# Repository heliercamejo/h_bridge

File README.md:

# H Bridge circuit
This circuit was following electronoobs youtube channel tutorial

[H_BRIDGE](https://electronoobs.com/eng_circuitos_tut1.php)

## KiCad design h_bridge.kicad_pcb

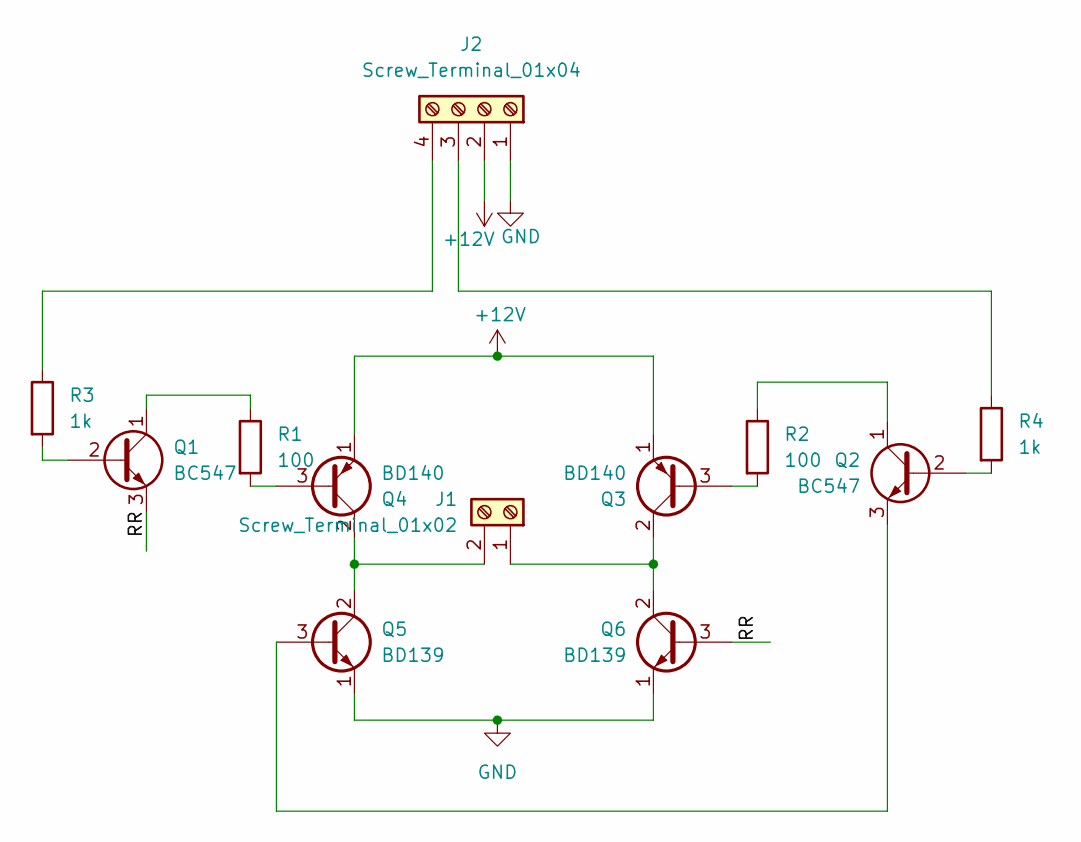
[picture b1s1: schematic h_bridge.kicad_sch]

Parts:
J1: Screw_Terminal_01x02; TerminalBlock_Phoenix_MKDS-1,5-2-5.08_1x02_P5.08mm_Horizont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
J2: Screw_Terminal_01x04; TerminalBlock_Phoenix_MKDS-1,5-4-5.08_1x04_P5.08mm_Horizont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
Q1, Q2: BC547; TO-92_Inline
Q3, Q4: BD140; TO-126-3_Vertical
Q5, Q6: BD139; TO-126-3_Vertical
R1, R2: 100; R_Axial_DIN0204_L3.6mm_D1.6mm_P7.62mm_Horizontal
R3, R4: 1k; R_Axial_DIN0204_L3.6mm_D1.6mm_P7.62mm_Horizontal

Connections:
+12V: J2.2, Q3.1 (E), Q4.1 (E)
/RR: Q1.3 (E), Q6.3 (B)
GND: J2.1, Q5.1 (E), Q6.1 (E)
unnamed: J1.1, Q3.2 (C), Q6.2 (C)
unnamed: J1.2, Q4.2 (C), Q5.2 (C)
unnamed: J2.3, R4.1
unnamed: J2.4, R3.1
unnamed: Q1.2 (B), R3.2
unnamed: Q1.1 (C), R1.1
unnamed: Q2.2 (B), R4.2
unnamed: Q2.1 (C), R2.1
unnamed: Q2.3 (E), Q5.3 (B)
unnamed: Q3.3 (B), R2.2
unnamed: Q4.3 (B), R1.2

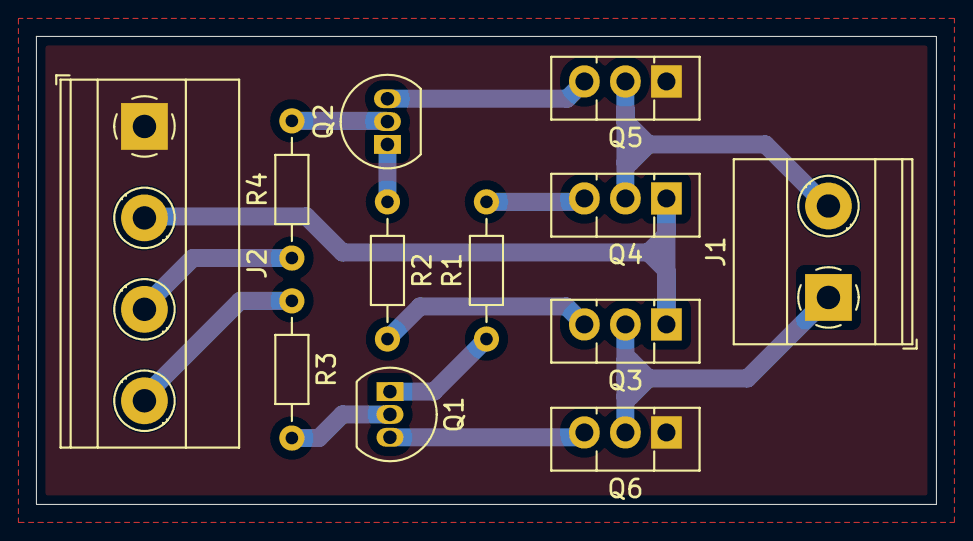
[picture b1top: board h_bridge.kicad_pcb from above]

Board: 2 copper layers, 50.0 x 26.0 mm, 12 parts (0 on the bottom side), 14 nets.
